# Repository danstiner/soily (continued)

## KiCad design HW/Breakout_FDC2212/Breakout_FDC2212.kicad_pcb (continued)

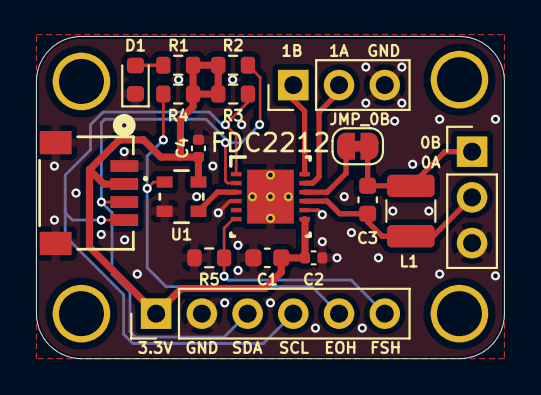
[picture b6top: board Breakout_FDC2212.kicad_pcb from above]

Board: 2 copper layers, 26.0 x 17.9 mm, 22 parts (0 on the bottom side), 13 nets.

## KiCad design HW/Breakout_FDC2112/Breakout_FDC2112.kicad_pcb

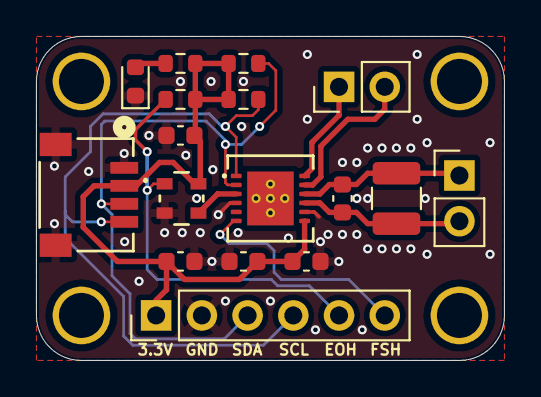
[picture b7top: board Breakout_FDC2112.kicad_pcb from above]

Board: 2 copper layers, 26.0 x 18.0 mm, 21 parts (0 on the bottom side), 12 nets.

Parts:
C1: 1u; C_0603_1608Metric
C2, C4: 0.1u; C_0603_1608Metric
C3: 0.01u; C_0603_1608Metric
C13: 33p; C_0603_1608Metric
D3: PWRLED; LED_0603_1608Metric
H1, H2, H3, H4: MountingHole; MountingHole_2.5mm_Plated
J1: SM04B-SRSS-TB; CONN_SM04B-SRSS-TB_JST
J2, J3: Conn_01x02; PinHeader_1x02_P2.54mm_Vertical
J4: Conn_01x06; PinHeader_1x06_P2.54mm_Vertical
L1: 10uH; L_1210_3225Metric
R1, R7, R8: 10k; R_0603_1608Metric
R4: 680; R_0603_1608Metric
U5: 625L3C040M00000; IC_625L3C040M00000_CTS
U6: FDC2112; DNT0012B_TEX

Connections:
+3.3V: C1.1, C2.1, C3.1, C4.1, J1.2, J4.1, R1.1, R4.1, R7.1, R8.1, U5.4 (VCC), U6.7 (VDD)
/EOH: J4.5, R1.2, U5.1 (EOH)
/FDC_CLK: U5.3 (OUTPUT), U6.3 (CLKIN)
/SCL: J1.4, J4.4, R8.2, U6.1 (SCL)
/SDA: J1.3, J4.3, R7.2, U6.2 (SDA)
/SENSE0+: C13.1, J2.2, L1.1, U6.9 (IN0A)
/SENSE0-: C13.2, J2.1, L1.2, U6.10 (IN0B)
/SENSE1+: J3.2, U6.11 (IN1A)
/SENSE1-: J3.1, U6.12 (IN1B)
/SHUTDOWN: J4.6, U6.6 (SD)
GND: C1.2, C2.2, C3.2, C4.2, D3.1 (K), J1.1, J1.5 (MT1), J1.6 (MT2), J4.2, U5.2 (GND), U6.4 (ADDR), U6.8 (GND)
unnamed: D3.2 (A), R4.2

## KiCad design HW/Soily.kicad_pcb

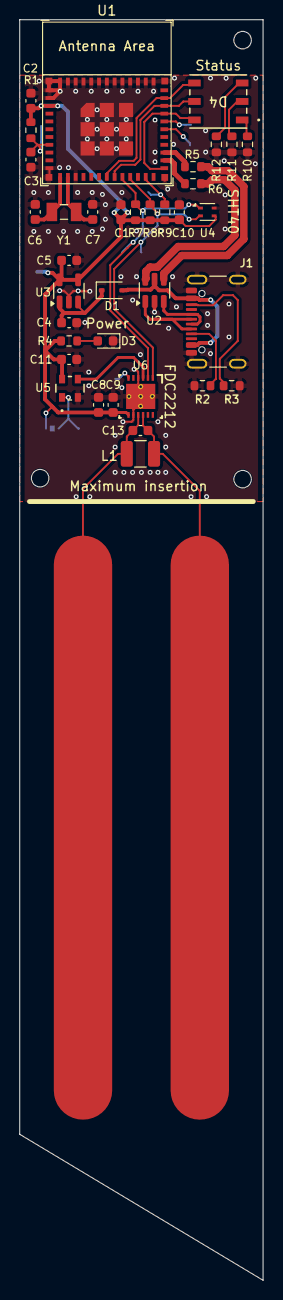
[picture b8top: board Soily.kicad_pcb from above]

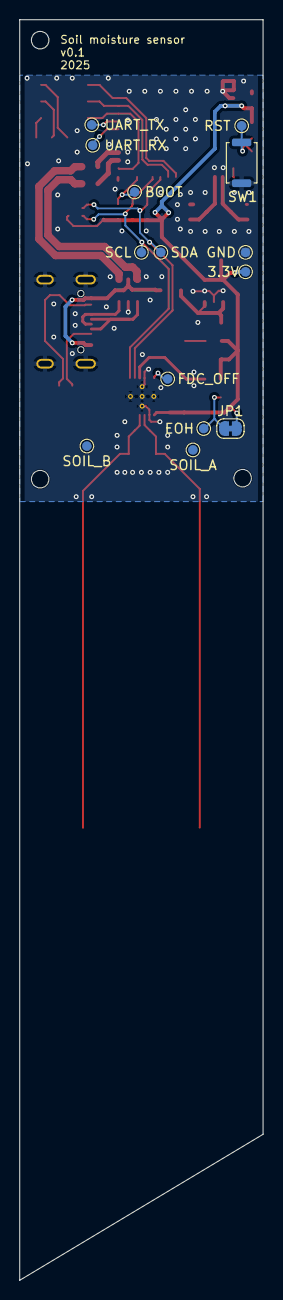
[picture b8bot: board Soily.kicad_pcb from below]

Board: 2 copper layers, 25.0 x 129.5 mm, 54 parts (14 on the bottom side), 32 nets.

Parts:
C1: 10u; C_0603_1608Metric
C2, C8, C10, C11: 0.1u; C_0603_1608Metric
C3, C4, C5: 1u; C_0603_1608Metric
C6, C7: 12p; C_0603_1608Metric
C9: 0.01u; C_0603_1608Metric
C12: SOIL; C_Rectangle
C13: 33p; C_0603_1608Metric
D1: B0520WS-7-F; D_SOD-323
D3: PWRLED; LED_0603_1608Metric
D4: 150505M173300; LED_150505M173300_WRE
H1, H2, H3: MountingHole; MountingHole_1.6mm_M1.6
J1: USB4105-GF-A; USB_C_Receptacle_GCT_USB4105-xx-A_16P_TopMnt_Horizontal
JP1: EOH; SolderJumper-2_P1.3mm_Bridged_RoundedPad1.0x1.5mm
L1: 18uH; L_1210_3225Metric
R1, R7, R8, R9: 10k; R_0603_1608Metric
R2, R3: 5.1k; R_0603_1608Metric
R4: 680; R_0603_1608Metric
R5, R6: 22; R_0603_1608Metric
R10: 60; R_0603_1608Metric
R11, R12: 10; R_0603_1608Metric
SW1: Reset; SW_Push_SPST_NO_Alps_SKRK
TP1: 3.3V; TestPoint_Pad_D1.0mm
TP2: GND; TestPoint_Pad_D1.0mm
TP3: BOOT; TestPoint_Pad_D1.0mm
TP4: RST; TestPoint_Pad_D1.0mm
TP5: UART_TX; TestPoint_Pad_D1.0mm
TP6: UART_RX; TestPoint_Pad_D1.0mm
TP7: SCL; TestPoint_Pad_D1.0mm
TP8: SDA; TestPoint_Pad_D1.0mm
TP9: SOIL_A; TestPoint_Pad_D1.0mm
TP10: EOH; TestPoint_Pad_D1.0mm
TP11: FDC_OFF; TestPoint_Pad_D1.0mm
TP12: SOIL_B; TestPoint_Pad_D1.0mm
U1: ESP32-H2-MINI-1
U2: USBLC6-2SC6; SOT-23-6
U3: AP2112K-3.3; SOT-23-5
U4: SHT40; Sensirion_DFN-4_1.5x1.5mm_P0.8mm_SHT4x_NoCentralPad
U5: 625L3C040M00000; IC_625L3C040M00000_CTS
U6: FDC2212; DNT0012B
Y1: ABS07-32.768KHZ-T; XTAL_ABS07-32.768KHZ-T

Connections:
+3.3V: C1.1, C2.1, C5.1, C8.1, C9.1, C10.1, C11.1, JP1.2 (B), R1.1, R4.1, R7.1, R8.1, R9.1, TP1.1, U1.3 (3V3), U3.4 (NC), U3.5 (VOUT), U4.3 (VDD), U5.4 (VCC), U6.7 (VDD)
/BOOTMODE: R9.2, TP3.1, U1.23 (GPIO9)
/D+: J1.A6 (D+), J1.B6 (D+), U2.3 (I/O2)
/D-: J1.A7 (D-), J1.B7 (D-), U2.1 (I/O1)
/EOH: JP1.1 (A), TP10.1, U5.1 (EOH)
/ESP_D+: R5.1, U1.27 (GPIO27/FSPICS5/USB_D+)
/ESP_D-: R6.1, U1.26 (GPIO26/FSPICS4/USB_D-)
/ESP_EN: C3.1, R1.2, SW1.1, TP4.1, U1.8 (EN)
/FDC_CLK: U5.3 (OUTPUT), U6.3 (CLKIN)
/FDC_OFF: TP11.1, U6.6 (SD)
/LED_B: D4.4 (BA), U1.18 (GPIO4/FSPICLK/ADC1_CH3/MTCK), U1.34 (NC)
/LED_G: D4.5 (GA), U1.19 (GPIO5/FSPID/ADC1_CH4/MTDI), U1.33 (NC)
/LED_R: D4.6 (RA), U1.25 (GPIO25/FSPICS3), U1.32 (NC)
/SCL: R8.2, TP7.1, U1.21 (GPIO11/ZCD1), U4.2 (SCL), U6.1 (SCL)
/SDA: R7.2, TP8.1, U1.20 (GPIO10/ZCD0), U4.1 (SDA), U6.2 (SDA)
/SENSE_SOIL+: C12.1, C13.1, L1.1, TP9.1, U6.9 (IN0A)
/SENSE_SOIL-: C12.2, C13.2, L1.2, TP12.1, U6.10 (IN0B)
/UART_RX: TP6.1, U1.30 (GPIO23/FSPICS1/U0RXD)
/UART_TX: TP5.1, U1.31 (GPIO24/FSPICS2/U0TXD)
/USB_D+: R5.2, U2.4 (I/O2)
/USB_D-: R6.2, U2.6 (I/O1)
/USB_VBUS: D1.2 (A), J1.A4 (VBUS), J1.A9 (VBUS), J1.B4 (VBUS), J1.B9 (VBUS), U2.5 (VBUS)
/XTAL_32K+: C6.1, U1.12 (GPIO13/XTAL_32K_P), Y1.1
/XTAL_32K-: C7.1, U1.13 (GPIO14/XTAL_32K_N), Y1.2
GND: C1.2, C2.2, C3.2, C4.2, C5.2, C6.2, C7.2, C8.2, C9.2, C10.2, C11.2, D3.1 (K), J1.A1 (GND), J1.A12 (GND), J1.B1 (GND), J1.B12 (GND), J1.S1 (SHIELD), R2.1, R3.2, R10.2, R11.2, R12.2, SW1.2, TP2.1, U1.1 (GND), U1.2 (GND), U1.11 (GND), U1.14 (GND), U1.36 (GND), U1.37 (GND), U1.38 (GND), U1.39 (GND), U1.40 (GND), U1.41 (GND), U1.42 (GND), U1.43 (GND), U1.44 (GND), U1.45 (GND), U1.46 (GND), U1.47 (GND), U1.48 (GND), U1.49 (GND), U1.50 (GND), U1.51 (GND), U1.52 (GND), U1.53 (GND), U2.2 (GND), U3.2 (GND), U4.4 (VSS), U5.2 (GND), U6.4 (ADDR), U6.8 (GND), U6.13 (PAD), U6.V (VIA)
unnamed: C4.1, D1.1 (K), U3.1 (VIN), U3.3 (EN)
unnamed: D3.2 (A), R4.2
unnamed: D4.3 (BK), R12.1
unnamed: D4.2 (GK), R11.1
unnamed: D4.1 (RK), R10.1
unnamed: J1.A5 (CC1), R2.2
unnamed: J1.B5 (CC2), R3.1

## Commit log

2025-09-09 Passing DRC
2025-09-09 Missing testpad connections
2025-09-10 Cleanup component selection
2025-09-11 FDC2212 Breakout board
2025-09-11 Align pin holes for potential breadboard mounting
2025-09-11 Soil probe breakouts
2025-09-16 BQ25570 Breakout
2025-09-24 FDC 2112 breakout
2025-09-24 FDC2212 breakout: delete extra user drawing
2025-10-03 esphome component for adafruit soil sensor
2025-10-03 FDC1004 progress and misc cleanup
2025-10-03 rough esphome component for fdc2x1x
2025-10-15 FDC2212v2
2025-10-15 NEH7100 breakout v1
2025-10-18 v1 FDC1004 breakout
2025-11-02 esphome fdc2x1x cleanup
2025-11-02 BQ25570 breakout v2
    - 1.8V output
    - Aligned headers for breadboarding
2025-11-02 Split gitignores and cleanup
2025-11-30 nrf54L hygrometer firmware
2025-12-09 nrf54L hygrometer prototype firmware
2025-12-09 tlv parse script
2025-12-09 Simplify log statement
2025-12-09 Larger shell stack and buffer to allow debug ot tlv programming
2025-12-09 Log tweak
2025-12-09 mcuboot board config
2025-12-09 Fix ICD support
2025-12-09 Note need for hex: prefix
2025-12-10 Configure thread role
2025-12-10 Enable SSED
